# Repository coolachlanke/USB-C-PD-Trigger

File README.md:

# USB-C PD Trigger Evaluation Board

---

## Overview
A custom 4-layer PCB for evaluating the triggering of various USB-C Power Delivery (PD) voltage profiles over I2C.
The board combines an STM32F401RBT6 microcontroller with a Cypress CYPD3177 PD sink controller, enabling flexible control and monitoring of USB-C PD outputs.

## Features

- **USB-C Input**
  - Receptacle with differential pair routing for DFU support
  - CYPD3177 PD sink controller with I2C interface to MCU
  - Default PDO profile via resistor divider

- **Microcontroller**
  - STM32F401RBT6
  - SWD header for programming/debugging
  - USB DFU capability for easy firmware flashing
  - I2C communication with PD controller

- **User Interface**
  - Single pushbutton to cycle through PDOs
  - 5x yellow indicator LEDs for 5 V, 9 V, 12 V, 15 V, 20 V

- **Connectivity**
  - VOUT terminal block for load connection
  - UART header (TX/RX) for serial monitoring

- **Debug/Monitoring**
  - Testpoints for VIN, VOUT, and GND

## Engineering Notes

- **Stackup:** 4 layers  
  - L1: Signal  
  - L2: Solid GND plane  
  - L3: Power plane  
  - L4: Signal

- **Differential Pair Routing (D+/D−)**
  - ~35 mm trace length  
  - ~0.9 mm mismatch (acceptable for USB Full Speed)  
  - Routed mainly on bottom layer with coplanar GND pour

- **Grounding**
  - Full-plane GND layers with stitching vias for shielding  
  - Top and bottom copper filled with GND pours

## Manufacturing
- Gerbers, BOM, and CPL generated using the [JLCPCB KiCad plugin](https://github.com/Bouni/kicad-jlcpcb-tools)
- Board fabricated and assembled by JLCPCB  

## Bring-Up
Board bring-up required several iterations of firmware and hardware debugging. Key steps and issues encountered are as follows:

- Initial Power & Communication: Testing supply rails and buck converter output voltage. Testing continuity between key nodes. Early tests confirmed basic 5V supply was working using older 'dumb' USB Type-A to C cables.

- Buck Converter Noise Issue: It seems that the reference schematic's inductor was oversized, and also lacked output capacitance. I was able to increase the output capacitance from 9.4uF to 2uF, which decreased pk-pk output ripple from ~650mV to ~150mV, but I was not satisfied with this given the sensitive nature of the electronics.

- Workaround: Desoldered the buck converter and soldered a wire to power VDDD directly from the CYPD3177’s internal regulator.

- Result: Elimiated noisy power supply from list of potential issues.

- Cable & PDO Negotiation Failures: Higher PDOs (>5 V) consistently failed when using e-marked or “smart” USB-C cables. The default 'strapping resistor' voltage was set to 5-15V, with the chip prioritising the higher value. Dumb USB Type-A to C cables would always work and give 5V using basic voltage divider Rp/Rd negotiation, but PD, which requires BMC digital comms, would not. I was even able to select higher PDOs such as 15V using the Kowsi USB-C sniffer device, and plug that voltage into the USB Type-C receptacle on the PCB very carefully as to only engage the VBUS and GND pins. 15V would appear on VIN, but the CYPD3177 naturally would not activate the PMOS load switch to enable VOUT. When I finally plugged the Kowski all the way in, the CC lines made contact, something went astray in the ESD array, and the device shuts off in ~300ms as indicated by the scope trace below.

- After many hours of debugging, the likely suspect was the ESD protection diode on VBUS avalanching at higher voltages (9–20 V), as it is rated for 6V reverse-biased. Fine for 5V, but not 9V or anything greater. I still have my doubts as to weather this was really the issue, as I artifically connected higher voltages to VBUS and it didnt short. Either way, desoldering the ESD array fixed the board's negotiation problems entirely. Correct 300kHz BMC comms can be seen on the CC lines in the scope trace below.

- Result: Successful negotiation of the resistor-strapped PDO, either 15V or 20V by shorting the V_BUS_MAX pin to 3V3.

- Firmware Bring-Up: The strapping resistor combinations provide an immediate PDO, as the CYPD3177 samples the voltage dividers at power-up. However, to have complete flexibility over the requested PDO we require an I2C host to control the CYPD. This is the role of the STM32F401 MCU. Using the [EZ-PD HPI](https://www.infineon.com/assets/row/public/documents/24/44/infineon-ez-pd-tm-bcr-plus-bcr-lite-host-processor-interface-specification-cypd3176-cypd3178-usermanual-en.pdf) (Host Processor Interface) specification, I was able to readthe CYPD's SLIICON_ID over I2C. 

- STM32 HAL routines were then implemented to read the CYPD3177's read-only registers. The data was fed into a nicely formatted buffer and sent to the PC over UART for debugging. The chip's negotiated VBUS (in mV) was accurately reported, and changed from 15V to 20V upon the shorting of V_BUS_MAX to 3V3. Other debug outputs were printed to confirm PD responses, i.e. PD_RESPONSE, CURRENT_PDO, CURRENT_RDO.

- Problem: I was able to read from any register I likey, but could not write/command the chip to select different PDOs. In order to negotiate custom PDO, one must first be able to build the valid 32-bit PDO words themselves, according to the USB PD Rev 3.2 spec. The structure is as follows.

- Using many DEC -> BIN -> HEX conversions all PDOs for 5V, 9V, 12V, 15V and 20V (all at 3A) were developed. Utilising the `union` data-type in C, the 'PDO payload' was built and a function was written to send the 12-byte payload over I2C.

- I had immense issues with this, from endian-ness to spec differences between the CYPD3176, 3178 and missing documentation for the 3177. Additionally, one cannot check (via I2C read) whether the payload was really stored in the correct memory location (starting 0x1800) or not. The CYPD simply outputs a cryptic status code on the PD_RESPONSE register.

- At this stage I thought the 3177 was not PDO write-capable, i.e. its I2C interface is merely for reading registers. However, I found the following GitHub repo [Rutronik CYPD3177 USB PD Control Example](https://github.com/RutronikSystemSolutions/RDK2_USB_Power_Delivery_I2C_Control/tree/master), in which the CYPD3177 is specifically targeted. Ignoring their modbus protocols and PD dev GUI, I dug into the cypd3177.h and cypd3177.c source files to see what they were doing differently. It appeared to be the same as what I was doing, except I was padding the remainder of the PDO payload with zeros, and the memory-write region can supposedly handle up to 7 PDOs with the newer CYPD3176 IC. After translating the Cypress-MCU HAL functions to their STM32 HAL analogs, I was able to use these library functions in my main.c script with functions such as `CYPD3177_ID(uint16_t *id);` and `CYPD3177_VBUS_mV(uint16_t *voltage);`. This seemed to work, as before, in read-only mode. However, to my surprise, when I tested `CYPD3177_ChangePDO(uint32_t *pdo);` with Rutronik's built in PDO1 of 9V @ 2A - it worked! The PCB successfully negotiated 9V from the Baseus PD source and it was verified by the multimeter! The magic function is as follows.

```
HAL_StatusTypeDef CYPD3177_ChangePDO(uint32_t *pdo) {
    union {
        uint8_t  data8[12];
        uint32_t data32[3];
    } pdo_data;

    pdo_data.data32[0] = 0x534E4B50; // "SNKP"
    pdo_data.data32[1] = pdo[0];
    pdo_data.data32[2] = pdo[1];

    if (CYPD3177_Write(CYPD_WRITE_DATA_MEM_REG, pdo_data.data8, sizeof(pdo_data.data8)) != HAL_OK)
        return HAL_ERROR;

    uint8_t mask = 0x03; // Enables, PDO0 amd PD1. Higher voltage => higher priority.
    if (CYPD3177_Write(CYPD_SELECT_SINK_PDO_CMD, &mask, 1) != HAL_OK)
        return HAL_ERROR;

    return HAL_OK;
}
```

- From here, transferred all my pre-computed PDOs and set up a script to change the PDO using `CYPD3177_ChangePDO(uint32_t *pdo);` via a button press (attached to pin PB7) to cycle 5V -> 9V -> 12V -> 15V -> 20V -> 5V. An indicator LED_n illumiated when PDO_n is asserted. Additionally, the STATUS LED illuminates when the CYPD successfully powers on, and the FAULT LED illuminates when the requested PDO cannot be negotiated (for example from a dumb USSB Type-A cable).

- Validation & Testing: used an electronic load to draw current at each PDO and confirm stability. Also tested the source's ablity to cut power when too much current is demanded by the sink. With a 3A current setting, I found the source shut off at about 3.5A. This will vary from source to source, thus motivating the use of an on-board current-sense resistor to trigger CYPD3177 overcurrent shutdown events. The image below shows the board drawing 58W from the Type-C cable, with the indicator LED showing that the device is negotiating 20V.

- Analysed live V_BUS reporting via UART debugging output to verify button pressed result in the desired PDO changed. Incorporated a delay to ensure PDOs cannot change more than once per 100ms. One can see UART messages in reponse to button presses below.

```
>> Requested PDO[0], V=5000 mV
VBUS: 5000 mV
>> Requested PDO[1], V=9000 mV
VBUS: 9000 mV
>> Requested PDO[2], V=12000 mV
VBUS: 12000 mV
>> Requested PDO[3], V=15000 mV
VBUS: 14900 mV
>> Requested PDO[4], V=20000 mV
VBUS: 19900 mV

```

- Confirmed stable long-duration operation at all available PDOs. Note that the integrated Dual PMOS is not ideal due to the higher R_DS(on). In the next revision, I will use discrete MOSFETs with lower R_DS(on) and better thermal performace. 3A loads can cause excessive heating of the dual-PMOS package.

## Future Development

With this project's successful conclusion, I will now move towards incorporating a buck-boost CCCV charger such that the system can appropriately and safely charge Li-ion batteries from a variety of USB PD sources.

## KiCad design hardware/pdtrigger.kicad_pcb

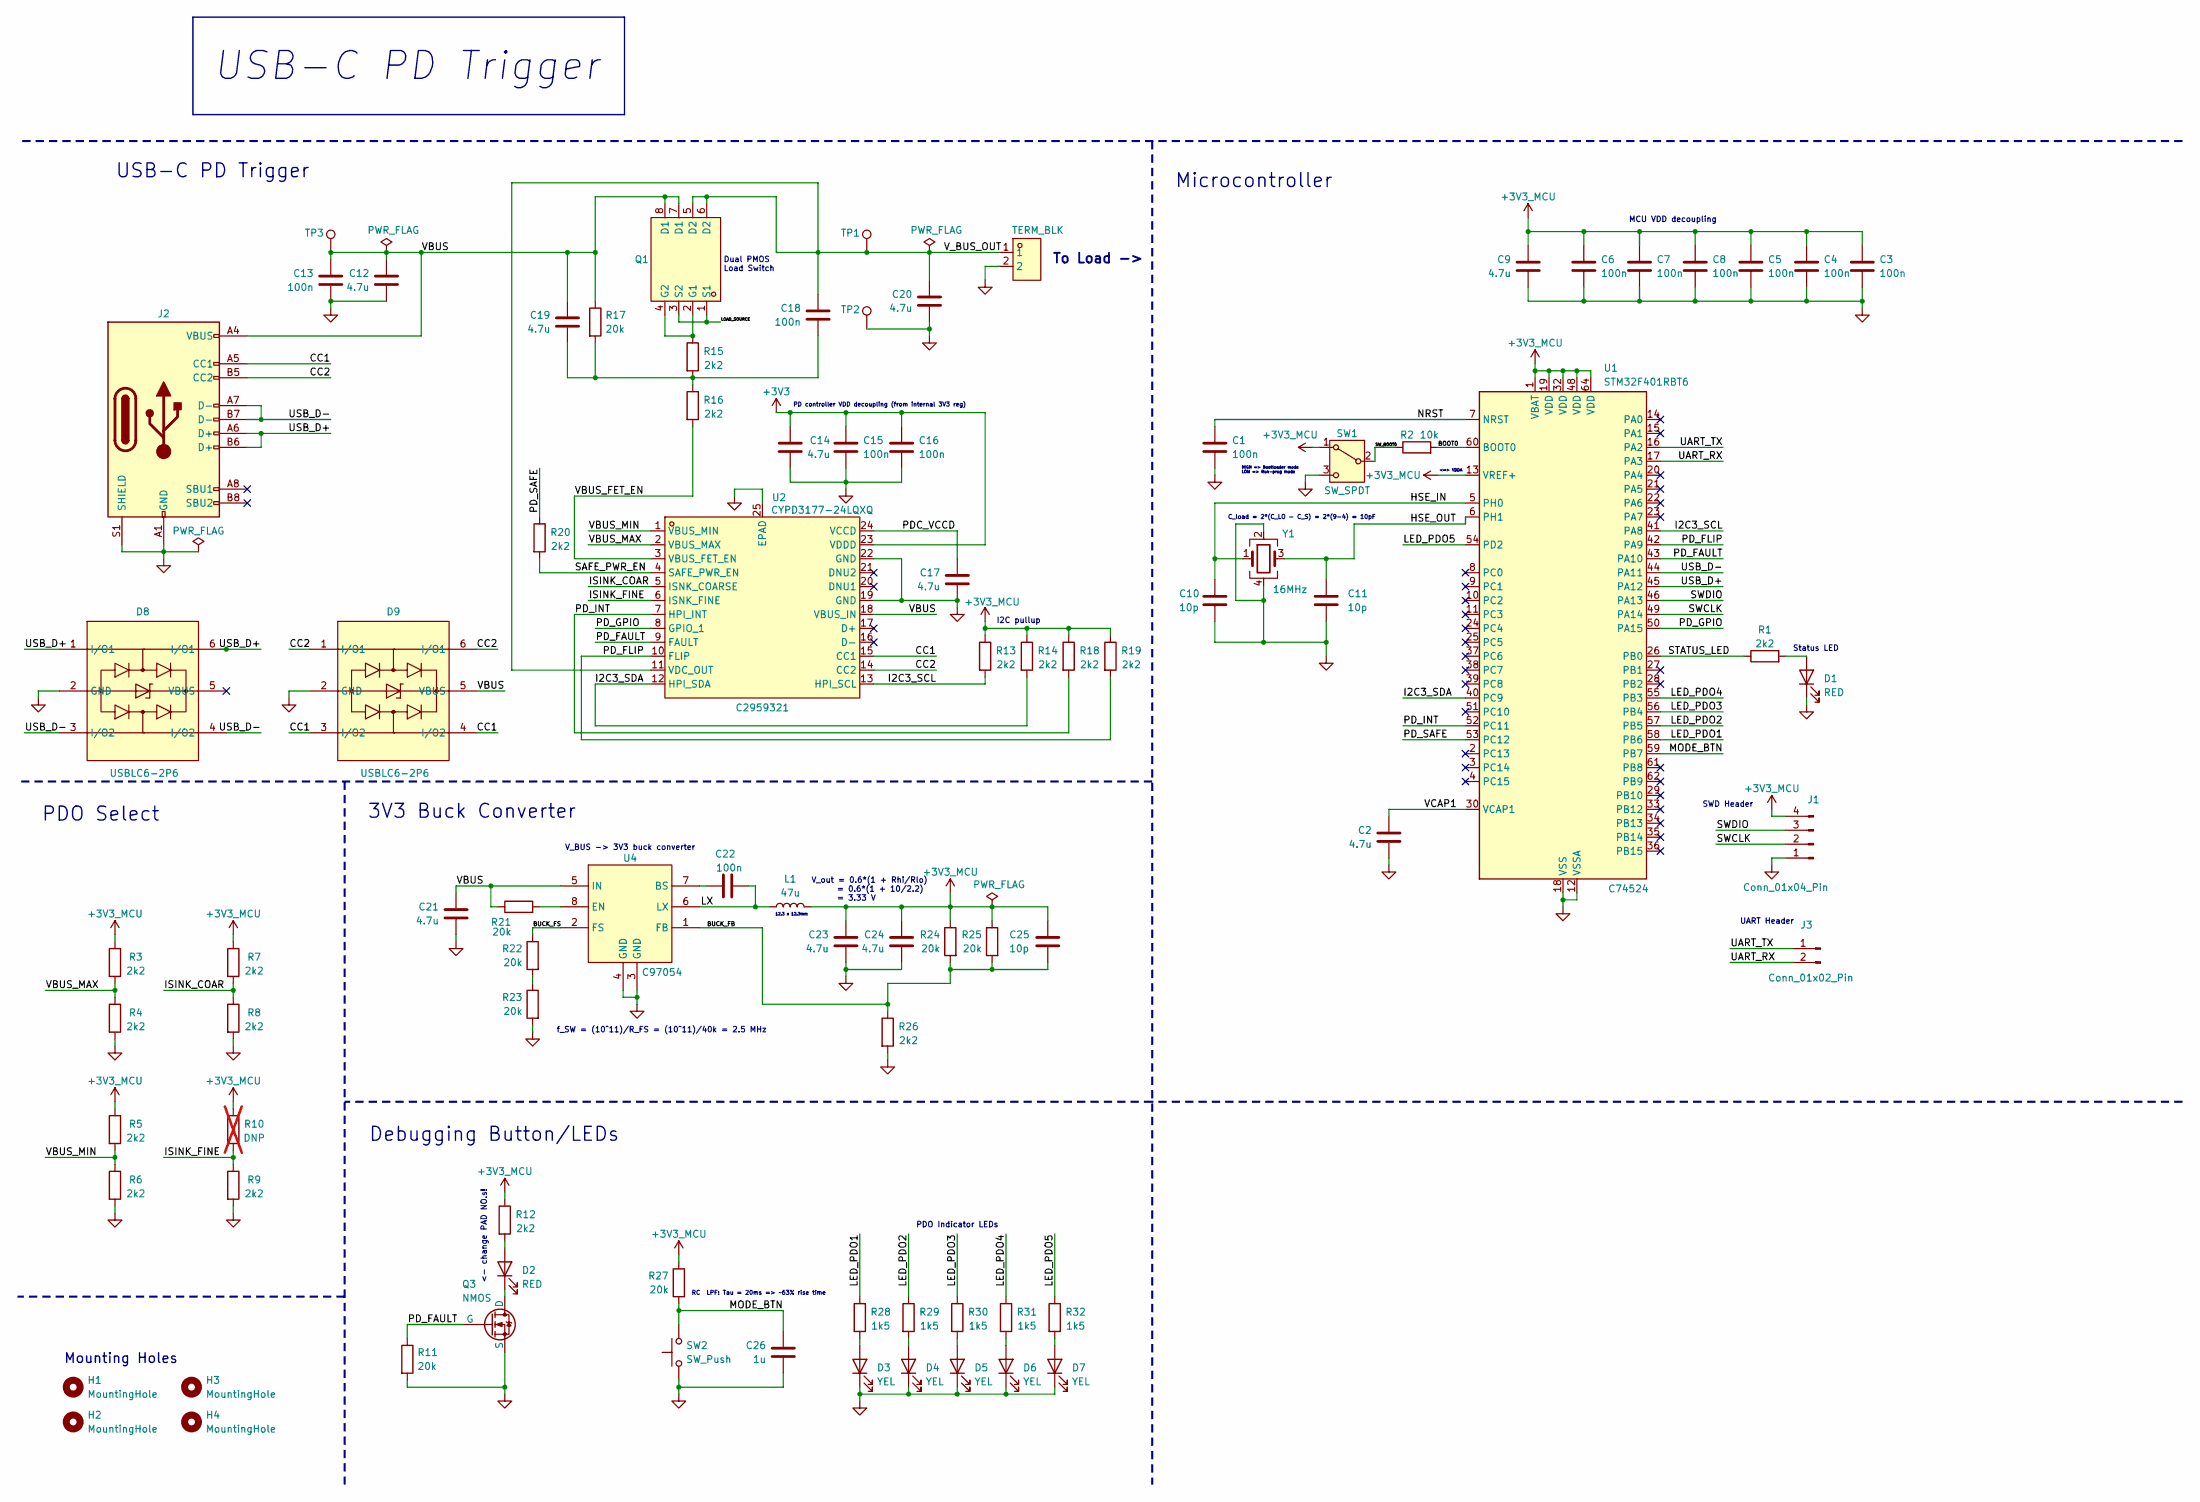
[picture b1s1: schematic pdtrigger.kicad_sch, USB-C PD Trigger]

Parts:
C1, C3, C4, C5, C6, C7, C8, C13, C15, C16, C18, C22: 100n; C_0402_1005Metric; LCSC C1525
C2, C9, C12, C14, C17, C19, C20, C21, C23, C24: 4.7u; C_0805_2012Metric; LCSC C1779
C10, C11, C25: 10p; C_0402_1005Metric; LCSC C32949
C26: 1u; C_0402_1005Metric; LCSC C52923
D1, D2: RED; LED_0805_2012Metric; LCSC C84256
D3, D4, D5, D6, D7: YEL; LED_0805_2012Metric; LCSC C2296
D8, D9: USBLC6-2P6; SOT-666-6_L1.6-W1.2-P0.50-LS1.6-BR; LCSC Part C15999
H1, H2, H3, H4: MountingHole; MountingHole_2.2mm_M2
J1: Conn_01x04_Pin; HDR-TH_4P-P2.54-V-M; LCSC C2691448
J2: USB_C_Receptacle_USB2.0_16P; NEW_USB-C-SMD_TYPE-C-6PIN-2MD-073; LCSC C2765186
J3: Conn_01x02_Pin; HDR-TH_2P-P2.54-V-M; LCSC C492401
L1: 47u; IND-SMD_L7.3-W7.3; LCSC C216198
Q1: DMP3098LSD-13; SO-8_L4.9-W3.9-P1.27-LS5.9-BL; LCSC Part C531177
Q3: NMOS; SOT-23-3_L2.9-W1.3-P1.90-LS2.4-BR; LCSC C8545
R1, R3, R4, R5, R6, R7, R8, R9, R12, R13, R14, R15, R16, R18, R19, R20, R26: 2k2; R_0603_1608Metric; LCSC C4190
R2: 10k; R_0402_1005Metric; LCSC C25744
R10: DNP; R_0603_1608Metric; LCSC C4190; not fitted
R11, R17, R21, R22, R23, R24, R25, R27: 20k; R_0603_1608Metric; LCSC C4184
R28, R29, R30, R31, R32: 1k5; R_0402_1005Metric; LCSC C25867
SW1: SW_SPDT; SW-SMD_K3-1280S-K1; LCSC C92658
SW2: SW_Push; SW-SMD_L3.9-W3.0-P4.45; LCSC C720477
TP1, TP2, TP3: TestPoint; TestPoint_THTPad_D1.5mm_Drill0.7mm
U1: STM32F401RBT6; LQFP-64_10x10mm_P0.5mm; LCSC C74524
U2: CYPD3177-24LQXQ; TQFN-24_L4.0-W4.0-P0.50-TL-EP2.8; LCSC Part C2959321
U3: TERM_BLK; CONN-TH_P5.00_KF301-5.0-2P; LCSC Part C474881
U4: SY8303AIC; TSOT-23-8_L2.9-W1.6-P0.65-LS2.8-BR; LCSC C97054
Y1: 16MHz; OSC-SMD_4P-L3.2-W2.5-BL; LCSC C13738

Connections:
+3V3: C14.1, C15.1, C16.1, U2.23 (VDDD)
+3V3_MCU: C3.1, C4.1, C5.1, C6.1, C7.1, C8.1, C9.1, C23.1, C24.1, C25.1, J1.4, L1.2, R3.1, R5.1, R7.1, R10.1, R12.1, R13.1, R14.1, R18.1, R19.1, R24.1, R25.1, R27.1, SW1.1 (A), U1.1 (VBAT), U1.13 (VREF+), U1.19 (VDD), U1.32 (VDD), U1.48 (VDD), U1.64 (VDD)
/BOOT0: R2.2, U1.60 (BOOT0)
/BUCK_FB: C25.2, R24.2, R25.2, R26.1, U4.1 (FB)
/BUCK_FS: R22.1, U4.2 (FS)
/CC1: D9.3 (I/O2), D9.4 (I/O2), J2.A5 (CC1), U2.15 (CC1)
/CC2: D9.1 (I/O1), D9.6 (I/O1), J2.B5 (CC2), U2.14 (CC2)
/HSE_IN: C10.1, U1.5 (PH0), Y1.1
/HSE_OUT: C11.1, U1.6 (PH1), Y1.3
/I2C3_SCL: R13.2, U1.41 (PA8), U2.13 (HPI_SCL)
/I2C3_SDA: R14.2, U1.40 (PC9), U2.12 (HPI_SDA)
/ISINK_COAR: R7.2, R8.1, U2.5 (ISNK_COARSE)
/ISINK_FINE: R9.1, R10.2, U2.6 (ISNK_FINE)
/LED_PDO1: R28.1, U1.58 (PB6)
/LED_PDO2: R29.1, U1.57 (PB5)
/LED_PDO3: R30.1, U1.56 (PB4)
/LED_PDO4: R31.1, U1.55 (PB3)
/LED_PDO5: R32.1, U1.54 (PD2)
/LOAD_SOURCE: Q1.1 (S1), Q1.3 (S2)
/LX: C22.2, L1.1, U4.6 (LX)
/MODE_BTN: C26.1, R27.2, SW2.2, U1.59 (PB7)
/NRST: C1.1, U1.7 (NRST)
/PDC_VCCD: C17.1, U2.24 (VCCD)
/PD_FAULT: Q3.2 (G), R11.1, U1.43 (PA10), U2.9 (FAULT)
/PD_FLIP: R19.2, U1.42 (PA9), U2.10 (FLIP)
/PD_GPIO: U1.50 (PA15), U2.8 (GPIO_1)
/PD_INT: R18.2, U1.52 (PC11), U2.7 (HPI_INT)
/PD_SAFE: R20.1, U1.53 (PC12)
/SAFE_PWR_EN: R20.2, U2.4 (SAFE_PWR_EN)
/STATUS_LED: R1.1, U1.26 (PB0)
/SWCLK: J1.2, U1.49 (PA14)
/SWDIO: J1.3, U1.46 (PA13)
/SW_BOOT0: R2.1, SW1.2 (B)
/UART_RX: J3.2, U1.17 (PA3)
/UART_TX: J3.1, U1.16 (PA2)
/USB_D+: D8.1 (I/O1), D8.6 (I/O1), J2.A6 (D+), J2.B6 (D+), U1.45 (PA12)
/USB_D-: D8.3 (I/O2), D8.4 (I/O2), J2.A7 (D-), J2.B7 (D-), U1.44 (PA11)
/VBUS_FET_EN: R16.2, U2.3 (VBUS_FET_EN)
/VBUS_MAX: R3.2, R4.1, U2.2 (VBUS_MAX)
/VBUS_MIN: R5.2, R6.1, U2.1 (VBUS_MIN)
/VCAP1: C2.1, U1.30 (VCAP1)
/V_BUS_OUT: C18.1, C20.1, Q1.5 (D2), Q1.6 (D2), TP1.1, U2.11 (VDC_OUT), U3.1; also elsewhere on the board
unnamed: C18.2, C19.2, R15.2, R16.1, R17.2
unnamed: D1.2 (A), R1.2
unnamed: D2.2 (A), R12.2
unnamed: D2.1 (K), Q3.1 (D)
unnamed: D3.2 (A), R28.2
unnamed: D4.2 (A), R29.2
unnamed: D5.2 (A), R30.2
unnamed: D6.2 (A), R31.2
unnamed: D7.2 (A), R32.2
unnamed: Q1.2 (G1), Q1.4 (G2), R15.1
unnamed: R22.2, R23.1
unnamed: C22.1, U4.7 (BS)
unnamed: R21.2, U4.8 (EN)

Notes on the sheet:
To Load ->
Microcontroller
V_out = 0.6*(1 + Rhi/Rlo) = 0.6*(1 + 10/2.2) = 3.33 V
PDO Indicator LEDs
<- change PAD NO.s!
SWD Header
C_load = 2*(C_LO - C_S) = 2*(9-4) = 10pF
UART Header
USB-C PD Trigger
12.3 x 12.3mm
PD controller VDD decoupling (from internal 3V3 reg)
MCU VDD decoupling
Mounting Holes
V_BUS -> 3V3 buck converter
Debugging Button/LEDs
RC LPF: Tau = 20ms => ~63% rise time
Dual PMOS Load Switch
Status LED
HIGH => Bootloader mode LOW => Run-prog mode
PDO Select
3V3 Buck Converter
I2C pullup
<=> VDDA
f_SW = (10^11)/R_FS = (10^11)/40k = 2.5 MHz

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
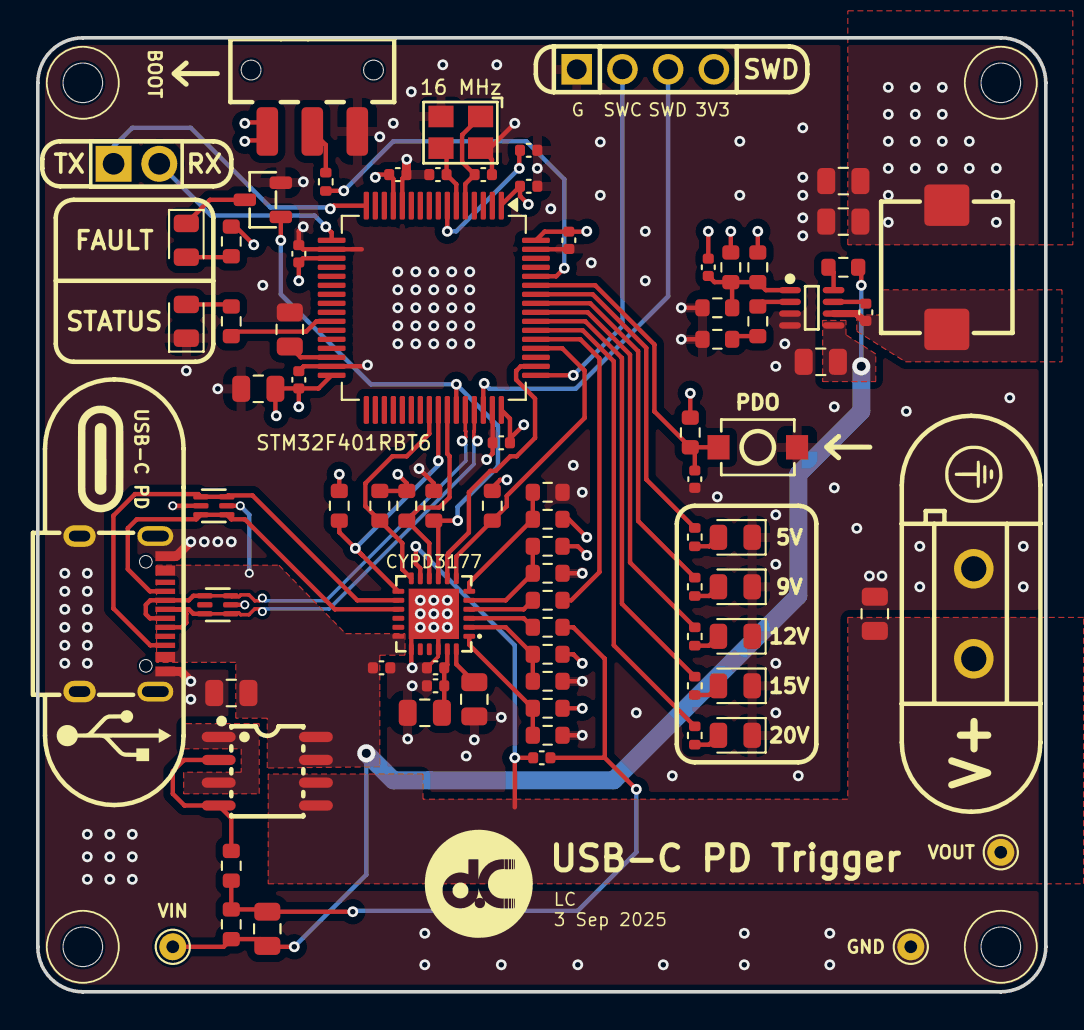
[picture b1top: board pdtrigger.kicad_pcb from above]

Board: 4 copper layers, 56.0 x 53.0 mm, 87 parts (0 on the bottom side), 57 nets.

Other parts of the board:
TP3#2, TP3#3: TestPoint; TestPoint_THTPad_D1.5mm_Drill0.7mm

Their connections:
/V_BUS_OUT: TP3#2.1; also elsewhere on the board

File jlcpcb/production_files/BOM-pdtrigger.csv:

Comment,Designator,Footprint,LCSC,Quantity
16MHz,Y1,OSC-SMD_4P-L3.2-W2.5-BL,C13738,1
100n,"C1,C13,C15,C16,C18,C22,C3,C4,C5,C6,C7,C8",C_0402_1005Metric,C1525,12
USBLC6-2P6,"D8,D9",SOT-666-6_L1.6-W1.2-P0.50-LS1.6-BR,C15999,2
4.7u,"C12,C14,C17,C19,C2,C20,C21,C23,C24,C9",C_0805_2012Metric,C1779,10
47u,L1,IND-SMD_L7.3-W7.3,C216198,1
YEL,"D3,D4,D5,D6,D7",LED_0805_2012Metric,C2296,5
10k,R2,R_0402_1005Metric,C25744,1
1k5,"R28,R29,R30,R31,R32",R_0402_1005Metric,C25867,5
Conn_01x04_Pin,J1,HDR-TH_4P-P2.54-V-M,C2691448,1
USB_C_Receptacle_USB2.0_16P,J2,NEW_USB-C-SMD_TYPE-C-6PIN-2MD-073,C2765186,1
CYPD3177-24LQXQ,U2,TQFN-24_L4.0-W4.0-P0.50-TL-EP2.8,C2959321,1
10p,"C10,C11,C25",C_0402_1005Metric,C32949,3
20k,"R11,R17,R21,R22,R23,R24,R25,R27",R_0603_1608Metric,C4184,8
2k2,"R1,R12,R13,R14,R15,R16,R18,R19,R20,R26,R3,R4,R5,R6,R7,R8,R9",R_0603_1608Metric,C4190,17
TERM_BLK,U3,CONN-TH_P5.00_KF301-5.0-2P,C474881,1
Conn_01x02_Pin,J3,HDR-TH_2P-P2.54-V-M,C492401,1
1u,C26,C_0402_1005Metric,C52923,1
DMP3098LSD-13,Q1,SO-8_L4.9-W3.9-P1.27-LS5.9-BL,C531177,1
SW_Push,SW2,SW-SMD_L3.9-W3.0-P4.45,C720477,1
STM32F401RBT6,U1,LQFP-64_10x10mm_P0.5mm,C74524,1
RED,"D1,D2",LED_0805_2012Metric,C84256,2
NMOS,Q3,SOT-23-3_L2.9-W1.3-P1.90-LS2.4-BR,C8545,1
SW_SPDT,SW1,SW-SMD_K3-1280S-K1,C92658,1
SY8303AIC,U4,TSOT-23-8_L2.9-W1.6-P0.65-LS2.8-BR,C97054,1
TestPoint,TP3,TestPoint_THTPad_D1.5mm_Drill0.7mm,,1

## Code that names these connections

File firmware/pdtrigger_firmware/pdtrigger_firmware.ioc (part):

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Mcu.Name=STM32F401R(B-C)Tx
Mcu.Package=LQFP64
Mcu.UserName=STM32F401RCTx
PA2.Mode=Asynchronous
PA2.Signal=USART2_TX
PA3.Mode=Asynchronous
PA3.Signal=USART2_RX
PA8.Mode=I2C
PA8.Signal=I2C3_SCL
PB0.GPIOParameters=GPIO_Speed,GPIO_PuPd,GPIO_ModeDefaultOutputPP
PB0.GPIO_ModeDefaultOutputPP=GPIO_MODE_OUTPUT_PP
PB0.GPIO_PuPd=GPIO_NOPULL
PB0.GPIO_Speed=GPIO_SPEED_FREQ_LOW
PB0.Signal=GPIO_Output
PB3.Signal=GPIO_Output
PB4.Signal=GPIO_Output
PB5.Signal=GPIO_Output
PB6.Signal=GPIO_Output
PB7.Signal=GPIO_Input
PC11.GPIOParameters=GPIO_PuPd,GPIO_ModeDefaultEXTI
PC11.GPIO_ModeDefaultEXTI=GPIO_MODE_IT_FALLING
PC11.GPIO_PuPd=GPIO_NOPULL
PC11.Signal=GPXTI11
PC9.Mode=I2C
PC9.Signal=I2C3_SDA
PD2.Signal=GPIO_Output
PH0\ -\ OSC_IN.Mode=HSE-External-Oscillator
PH0\ -\ OSC_IN.Signal=RCC_OSC_IN
PH1\ -\ OSC_OUT.Mode=HSE-External-Oscillator
PH1\ -\ OSC_OUT.Signal=RCC_OSC_OUT
RCC.HSE_VALUE=16000000
RCC.SYSCLKFreq_VALUE=84000000
RCC.SYSCLKSource=RCC_SYSCLKSOURCE_PLLCLK
board=custom

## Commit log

2025-09-01 Initial ICs and passives
2025-09-01 70% finished with component selection and schem entry
2025-09-01 Final wiring before leaving office
2025-09-03 Board ready for routing
2025-09-04 Added render image
2025-09-04 Update README.md again
2025-09-04 Cleaned up schem
2025-09-05 gitignore KiCAD .lck files
2025-09-05 rm cached
2025-09-05 more gitignore
2025-09-05 chore: untrack KiCad autosave/lock/backup files
2025-09-05 more README.md updates
2025-09-05 readme
2025-09-05 tweak
2025-09-05 again try
2025-09-05 added GND via-in-pad to CYPD3177 IC
2025-09-05 Prettier schematic
2025-09-08 Changed as per design review
2025-09-18 firmware work
2025-09-19 Hardware debugging
2025-09-26 firmware work after finally debugging hardware
2025-09-29 significant firmware work with i2c
2025-09-30 significant firmware work
2025-10-01 toiling with firmware
2025-10-02 firmware & PD board finally working (confetti emoji)
2025-10-03 project complete and documented
2025-10-03 spelling
